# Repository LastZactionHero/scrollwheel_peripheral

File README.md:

# Scrollwheel Peripheral Project

This is a KiCad project for a scrollwheel peripheral device.

## Library Management

This project includes a library management tool that helps organize components and datasheets.

### Using the Library Manager

1. Place your component files in the following directories:
   - `imports/parts/` - Parts downloaded from componentsearchengine.com or similar
   - `imports/datasheets/` - PDF datasheets for components

2. Run the library manager:
   ```
   python kicad_library_manager.py
   ```

3. The tool will:
   - Extract and organize symbols, footprints, and 3D models from imported parts
   - Organize datasheets for easy reference
   - Create library table files (`sym-lib-table` and `fp-lib-table`)
   - Update the project file with new library references

### Directory Structure

After running the tool, you'll have the following organized structure:

```
project/
├── imports/               # Original imported files
│   ├── datasheets/        # Original datasheets
│   └── parts/             # Original part files
├── library/               # Organized libraries
│   ├── symbols/           # Symbol libraries (.lib, .kicad_sym)
│   ├── footprints/        # Footprint libraries (.kicad_mod)
│   ├── models/            # 3D models (.stp, .wrl)
│   └── datasheets/        # Organized datasheets by manufacturer
├── sym-lib-table          # Symbol library table
├── fp-lib-table           # Footprint library table
├── kicad_library_manager.py  # The library management tool
└── [project files]        # KiCad project files
```

### Adding New Components

To add new components to your project:

1. Download the component files and datasheets
2. Place them in the appropriate import directories
3. Run the library manager again
4. Open your KiCad project, and the new libraries will be available

## Development Notes

- The library manager preserves your original files in the imports directory
- Datasheets are organized by manufacturer name (extracted from filename)
- Symlink tables are created to make libraries accessible in KiCad

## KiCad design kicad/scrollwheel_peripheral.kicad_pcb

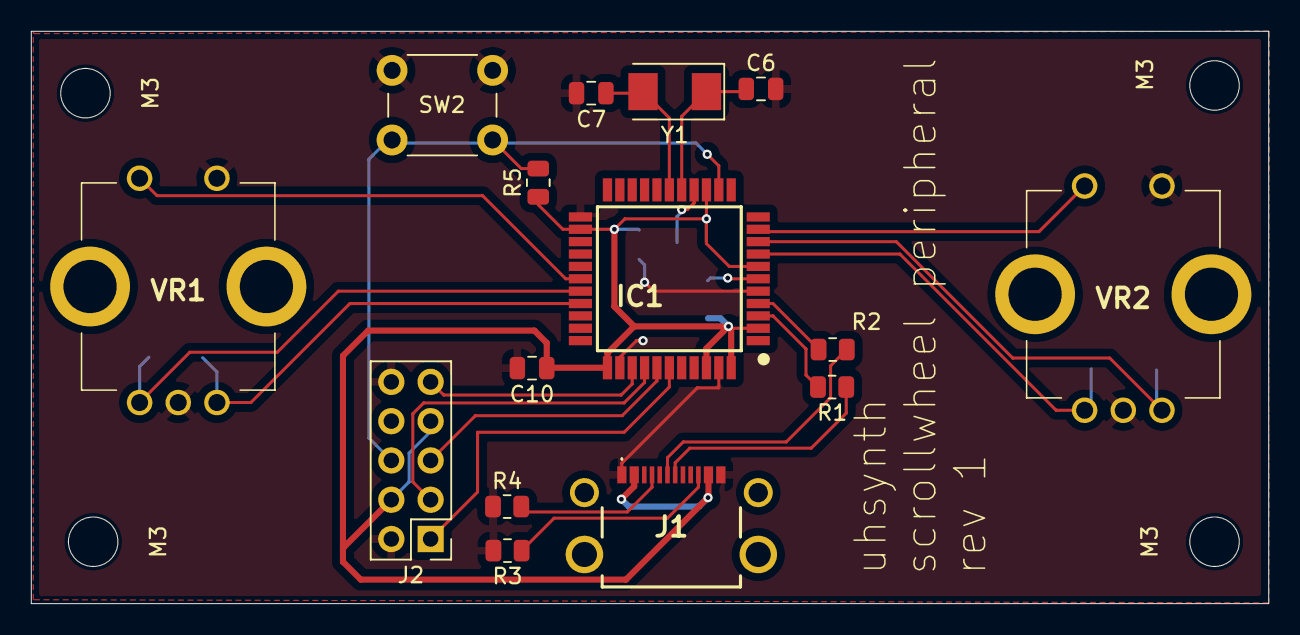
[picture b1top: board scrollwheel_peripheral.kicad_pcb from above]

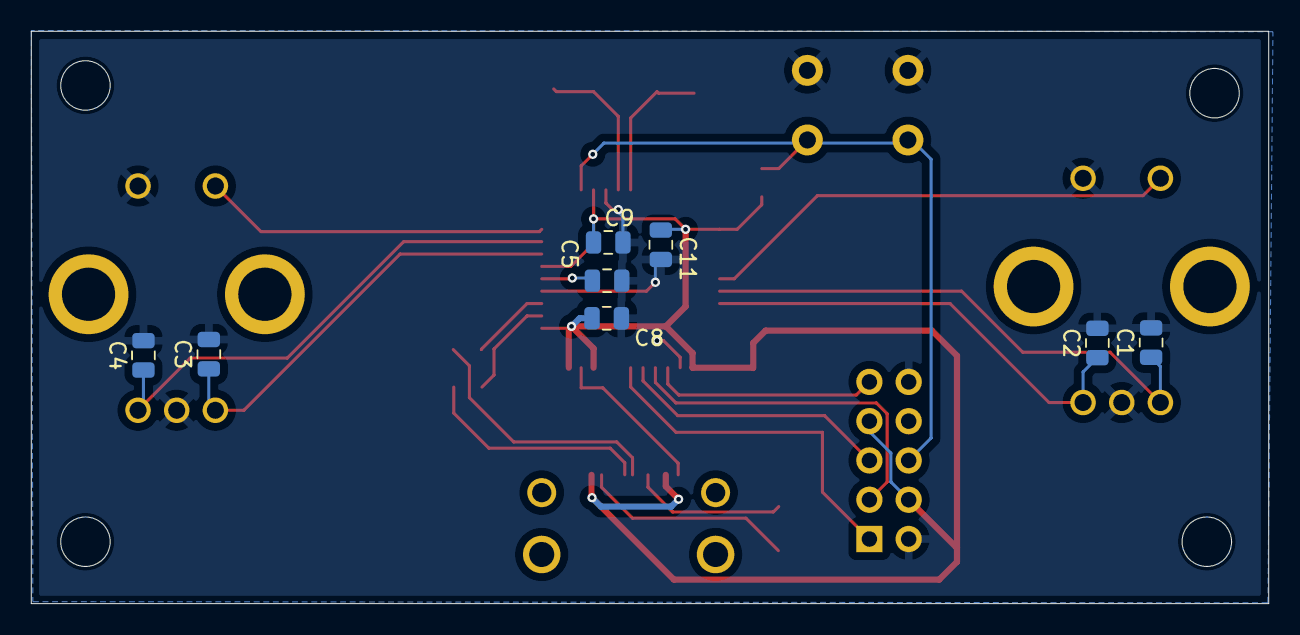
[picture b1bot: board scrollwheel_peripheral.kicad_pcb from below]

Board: 2 copper layers, 80.0 x 37.0 mm, 27 parts (8 on the bottom side), 22 nets.

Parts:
C1, C2, C3, C4, C8, C9, C10, C11: C; C_0805_2012Metric
C5: 0.1uF; C_0805_2012Metric
C6, C7: 22pF; C_0805_2012Metric
IC1: ATMEGA32U4-AU; QFP80P1200X1200X120-44N
J1: UJ20-C-H-G-MSMT-4-P16-TR; UJ20CHGMSMT4P16TR
J2: AVR-JTAG-10; PinHeader_2x05_P2.54mm_Vertical
M3, M3#2, M3#3, M3#4: MountingHole_3.2mm_M3
R1, R2: 22; R_0805_2012Metric
R3, R4: 5.1; R_0805_2012Metric
R5: 10k; R_0805_2012Metric
SW2: SW_Push; SW_PUSH_6mm
VR1, VR2: PEC11R-4220F-S0024; PEC11R4220FS0024
Y1: Crystal; Crystal_SMD_Abracon_ABM3-2Pin_5.0x3.2mm

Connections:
/5V: C8.2, C9.1, C10.1, C11.1, IC1.2 (UVCC), IC1.7 (VBUS), IC1.14 (VCC_1), IC1.24 (AVCC_1), IC1.34 (VCC_2), IC1.42 (AREF), IC1.44 (AVCC_2), J1.A4 (VBUS_1), J1.B4 (VBUS_2), J2.4 (VREF), J2.7 (VCC), R5.1
GND: C1.2, C2.2, C3.2, C4.2, C5.2, C6.2, C7.2, C8.1, C9.2, C10.2, C11.2, IC1.5 (UGND), IC1.15 (GND_1), IC1.23 (GND_2), IC1.35 (GND_3), IC1.43 (GND_4), J1.A1 (GND_1), J1.B1 (GND_2), J2.2 (GND), J2.10 (GND), R3.2, R4.1, SW2.1, VR1.2, VR1.C1 (C), VR2.2, VR2.C1 (C)
unnamed: C4.1, IC1.9 ((PCINT1/SCLK)_PB1), VR2.B1 (B)
unnamed: IC1.10 ((PDI/PCINT2/MOSI)_PB2), VR2.1
unnamed: C3.1, IC1.8 ((SS/PCINT0)_PB0), VR2.A1 (A)
unnamed: IC1.4 (D+), R2.2
unnamed: IC1.3 (D-), R1.2
unnamed: IC1.28 (PB4_(PCINT4/ADC11)), VR1.1
unnamed: C1.1, IC1.29 (PB5_(PCINT5/OC1A/~OC4B/ADC)), VR1.A1 (A)
unnamed: C2.1, IC1.30 (PB6_(PCINT6/OC1B/OC4B/ADC)), VR1.B1 (B)
unnamed: IC1.39 (PF4_(ADC4/TCK)), J2.1 (TCK)
unnamed: IC1.38 (PF5_(ADC5/TMS)), J2.5 (TMS)
unnamed: IC1.37 (PF6_(ADC6/TDO)), J2.3 (TDO)
unnamed: IC1.36 (PF7_(ADC7/TDI)), J2.9 (TDI)
unnamed: C5.1, IC1.6 (UCAP)
unnamed: C7.1, IC1.17 (XTAL1), Y1.2
unnamed: C6.1, IC1.16 (XTAL2), Y1.1
unnamed: IC1.13 (~RESET), J2.6 (~SRST), R5.2, SW2.2
unnamed: J1.A5 (CC1), R4.2
unnamed: J1.B5 (CC2), R3.1
unnamed: J1.A7 (DN1), R1.1
unnamed: J1.A6 (DP1), R2.1

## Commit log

2025-03-10 Scrollwheel board
2025-03-10 Misc changes
2025-03-12 Misc
2025-03-12 Schematic with Atmega
2025-03-12 footprints
2025-03-12 Part selection; Board
2025-03-12 More routing
2025-03-12 Moving stuff
2025-03-14 Finish routing for rev 1
